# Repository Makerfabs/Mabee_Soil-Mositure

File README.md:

# Mabee_Soil-Mositure

```
version:      1.0
Author:       Ricardo
Create Date:	2023/3/21
```

## Makerfabs

[Makerfabs home page](https://www.makerfabs.com/)

[Makerfabs Wiki](https://wiki.makerfabs.com/)

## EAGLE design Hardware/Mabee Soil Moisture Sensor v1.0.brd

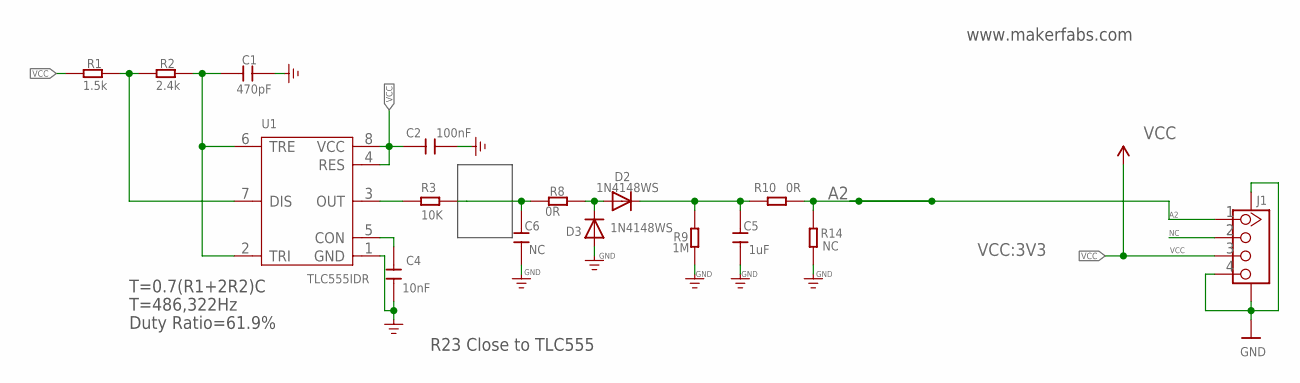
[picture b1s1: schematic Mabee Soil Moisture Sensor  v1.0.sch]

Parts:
C1: 470pF; C0603
C2: 100nF; C0603
C4: 10nF; C0603
C5: 1uF; DISCRETE_C0603
C6: NC; DISCRETE_C0603
D2, D3: 1N4148WS; SOD-323F
J1: J1; HW4-SMD-2.0-90D
R1: 1.5k; R0603
R2: 2.4k; R0603
R3: 10K; R0603
R8, R10: 0R; R0603
R9: 1M; R0603
R14: NC; R0603
U1: TLC555IDR; SOIC8-1.27-5X4MM

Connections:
A2: J1.1, R10.2, R14.1
GND: C1.1, C2.1, C4.2, C5.1, C6.1, D3.A, J1.4, J1.SS1, J1.SS2, R9.1, R14.2, U1.1 (GND)
unnamed: R1.1, R2.2, U1.7 (DIS)
unnamed: C1.2, R2.1, U1.2 (TRI), U1.6 (TRE)
unnamed: C4.1, U1.5 (CON)
unnamed: R3.1, U1.3 (OUT)
unnamed: C6.2, R3.2, R8.1
unnamed: D2.A, D3.C, R8.2
unnamed: C5.2, D2.C, R9.2, R10.1
NC: J1.2
VCC: C2.2, J1.3, R1.2, U1.4 (RES), U1.8 (VCC)

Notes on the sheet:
R23 Close to TLC555
www.makerfabs.com
T=0.7(R1+2R2)C
T=486,322Hz
Duty Ratio=61.9%
VCC:3V3

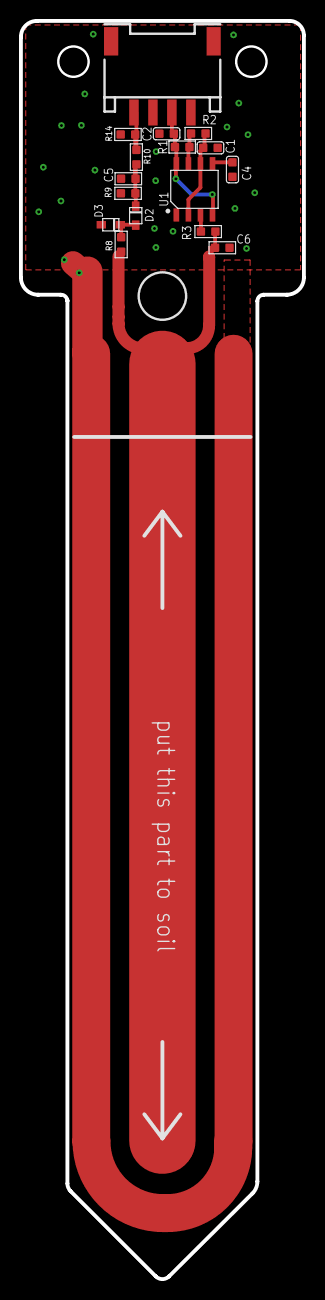
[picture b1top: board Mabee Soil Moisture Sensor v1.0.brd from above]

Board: 2 copper layers, 29.8 x 132.6 mm, 17 parts (1 on the bottom side), 10 nets.

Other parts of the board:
U$7: MAKERFABS_0.3

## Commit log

2023-03-21 Create Hardware
2023-03-24 Using for ESP32-S3
2023-03-27 update the readme

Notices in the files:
parts and their libraries:
SparkFun-Aesthetics: Licensing: Creative Commons ShareAlike 4.0 International - https://creativecommons.org/licenses/by-sa/4.0
microbuilder: This work is placed in the public domain, and may be freely used for commercial and non-commercial work with the following conditions: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
